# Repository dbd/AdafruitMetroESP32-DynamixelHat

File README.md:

# AdafruitMetroESP32-DynamixelHat

A HAT designed for the [AdaFruit Metro ESP32-S3](https://learn.adafruit.com/adafruit-metro-esp32-s3) to communicate with Dynamixel servos using this [library](https://github.com/dbd/CircuitPythonDynamixel)

# Bill of Materials
| Item | Link | Quantity | Unit Cost | Item Cost |
| ---- | ---- | -------- | --------- | --------- |
| TXB0104PWR Level Shifter | [Link](https://www.digikey.com/short/qm0td78w) | 1 | $0.87 | $0.87 | 
| SN74LVC2G241DCTR Tri-state buffer | [Link](https://www.digikey.com/short/1w0w74jb) | 1 | $0.40 | $0.40 | 
| 10k Resistor | [Link](https://www.digikey.com/short/27n7pcz3) | 4 | $0.10 | $0.40 | 
| 0.1 µF Capacitor | [Link](https://www.digikey.com/short/hjtz927q) | 6 | $0.10 | $0.60 | 
| 100 µF Capacitor | [Link](https://www.digikey.com/short/43pqprtd) | 1 | $1.73 | $1.73 | 
| JST Header | [Link](https://www.digikey.com/short/h1hjcqr2) | 3 | $0.46 | $1.38 | 
| 8P Header | [Link](https://www.digikey.com/short/35q99nnb) | 2 | $1.42 | $2.84 | 
| 6P Header | [Link](https://www.digikey.com/short/1hd3z8d7) | 1 | $1.80 | $1.80 | 
| 10P Header | [Link](https://www.digikey.com/short/rm5nhzqt) | 1 | $2.19 | $2.19 | 
| PCB Fab | | 5 | 2 | ~$20 |
| | | | Total Cost | $32.21|

# Assembly
Hand soldering this is not for the faint of heart. If you don't own a hotplate and solder paste I would recommend having your PCB fab doing all the SMD component assembly and then purchasing the 100 µF capacitor and headers to solder yourself. 
Otherwise all components are labeled and assuming your PCB has silk screen printing, it should just be matching footprints. 
A "cheap" hotplate can be found for ~$55 on Amazon and should be sufficient with some cheap solder paste in a syringe to go along.

If the JST connectors don't match the footprint, try inserting them the otherway. Incorrectly soldering them shouldn't cause harm since the 12v line is in the middele regardless but I don't recommend finding out.

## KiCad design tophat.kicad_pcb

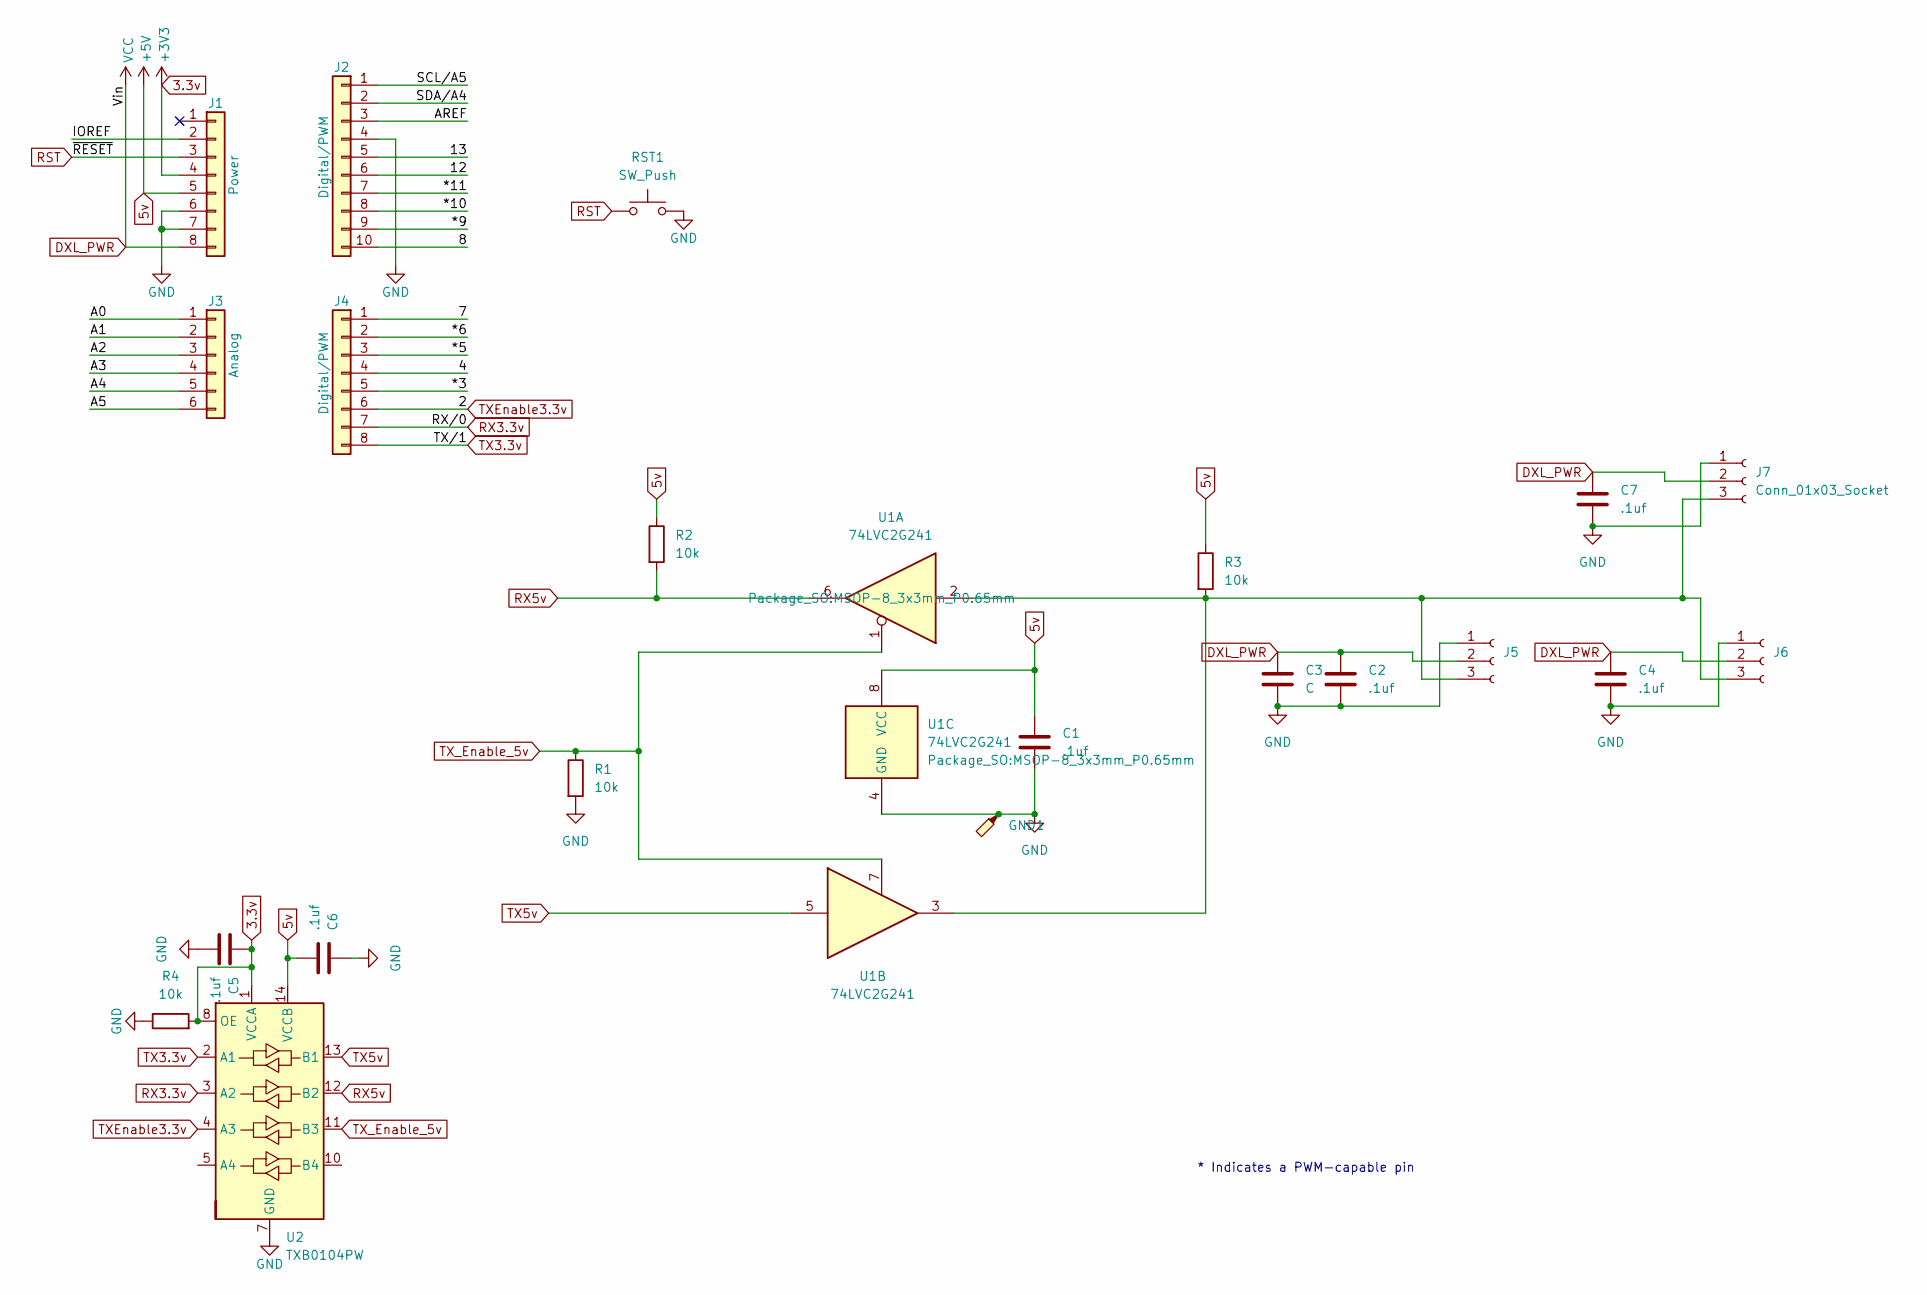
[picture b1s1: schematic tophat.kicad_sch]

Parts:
C1, C2, C4, C5, C6, C7: .1uf; 0805
C3: C; CP_Elec_8x6.2
GND1: TestPoint_Probe; TestPoint_Pad_1.0x1.0mm
J1: Power; PinSocket_1x08_P2.54mm_Vertical
J2: Digital/PWM; PinSocket_1x10_P2.54mm_Vertical
J3: Analog; PinSocket_1x06_P2.54mm_Vertical
J4: Digital/PWM; PinSocket_1x08_P2.54mm_Vertical
J5, J6, J7: Conn_01x03_Socket; JST_EH_B3B-EH-A_1x03_P2.50mm_Vertical
R1, R2, R3, R4: 10k; 0805
RST1: SW_Push; SW_Tactile_SPST_NO_Straight_CK_PTS636Sx25SMTRLFS
U1: 74LVC2G241; MSOP-8_3x3mm_P0.65mm
U2: TXB0104PW; TSSOP-14_4.4x5mm_P0.65mm

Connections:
3.3v: C5.1, J1.4, R4.2, U2.1 (VCCA), U2.8 (OE)
5v: C1.1, C6.2, J1.5, R2.1, R3.1, U1.8 (VCC), U2.14 (VCCB)
/4: J4.4
/7: J4.1
/8: J2.10
/12: J2.6
/13: J2.5
/*3: J4.5
/*5: J4.3
/*6: J4.2
/*9: J2.9
/*10: J2.8
/*11: J2.7
/A0: J3.1
/A1: J3.2
/A2: J3.3
/A3: J3.4
/A4: J3.5
/A5: J3.6
/AREF: J2.3
/IOREF: J1.2
/SCL/A5: J2.1
/SDA/A4: J2.2
DXL_PWR: C2.1, C3.1, C4.1, C7.1, J1.8, J5.2, J6.2, J7.2
GND: C1.2, C2.2, C3.2, C4.2, C5.2, C6.1, C7.2, GND1.1, J1.6, J1.7, J2.4, J5.1, J6.1, J7.1, R1.2, R4.1, RST1.2, U1.4 (GND), U2.7 (GND)
unnamed: J5.3, J6.3, J7.3, R3.2, U1.2, U1.3
RST: J1.3, RST1.1
RX3.3v: J4.7, U2.3 (A2)
RX5v: R2.2, U1.6, U2.12 (B2)
TX3.3v: J4.8, U2.2 (A1)
TX5v: U1.5, U2.13 (B1)
TXEnable3.3v: J4.6, U2.4 (A3)
TX_Enable_5v: R1.1, U1.1, U1.7, U2.11 (B3)

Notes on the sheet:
* Indicates a PWM-capable pin

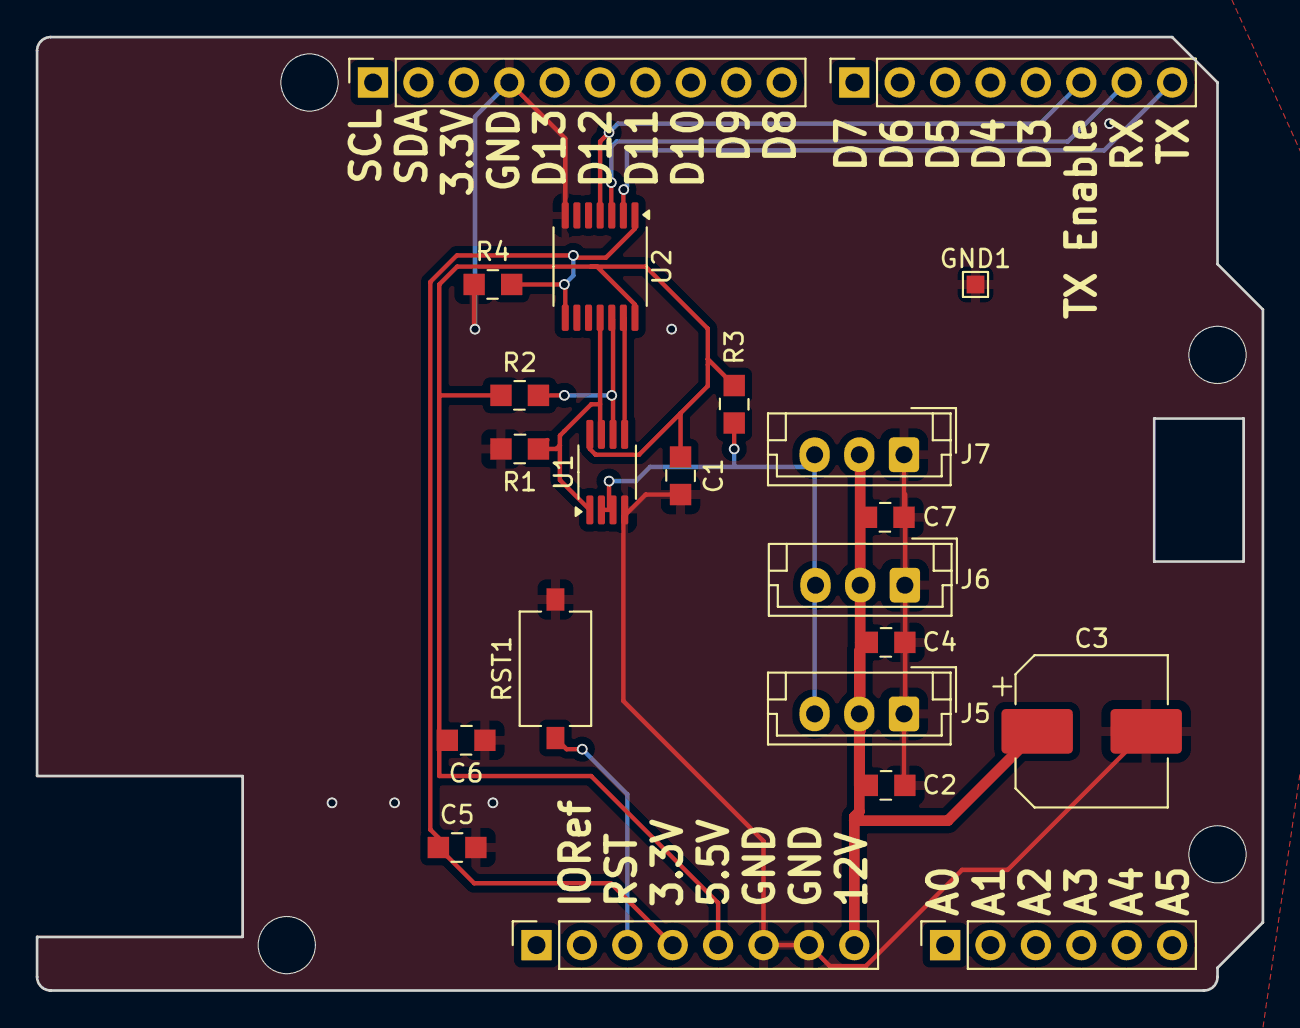
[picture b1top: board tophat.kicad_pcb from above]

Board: 2 copper layers, 68.6 x 53.3 mm, 26 parts (0 on the bottom side), 12 nets.

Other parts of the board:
MH1, MH2, MH3, MH4: MountingHole_3.2mm

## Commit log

2025-01-16 Update README.md
    Add a picture
2025-01-16 Add BOM
2025-01-16 Add tristate buffer name
2025-01-16 Add silk screen and fix up schematic
2025-01-16 Update picture
2025-01-17 typo in readme
